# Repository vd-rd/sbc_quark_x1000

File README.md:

## Overview
This module, based on Intel Quark X1020D microprocessor, is intended as a learning exercise in designing an embedded Linux board suitable for IoT applications with a focus on broad connectivity. All the board resources and documentation is open source and can be contributed to.

### Specifications
The board is composed of:
  * Intel Quark X1020 microprocessor
  * 256MB DDR3 RAM
  * NOR flash memory for UEFI and loader
  * MicroSD connector for rootfs and user storage
  * Expansion header with common functions available (USART, SPI, I2C etc.)
  * mPCIexpress header with both full and half size card support.

### Resources
You can find all necesary information to build or evaluate the module here:
   - [View layout and schematic](.) 
   - [View 3D board render](https://a360.co/2vnUFIM)
   - [Fabrication files](https://github.com/vd-rd/sbc_quark_x1000/releases)

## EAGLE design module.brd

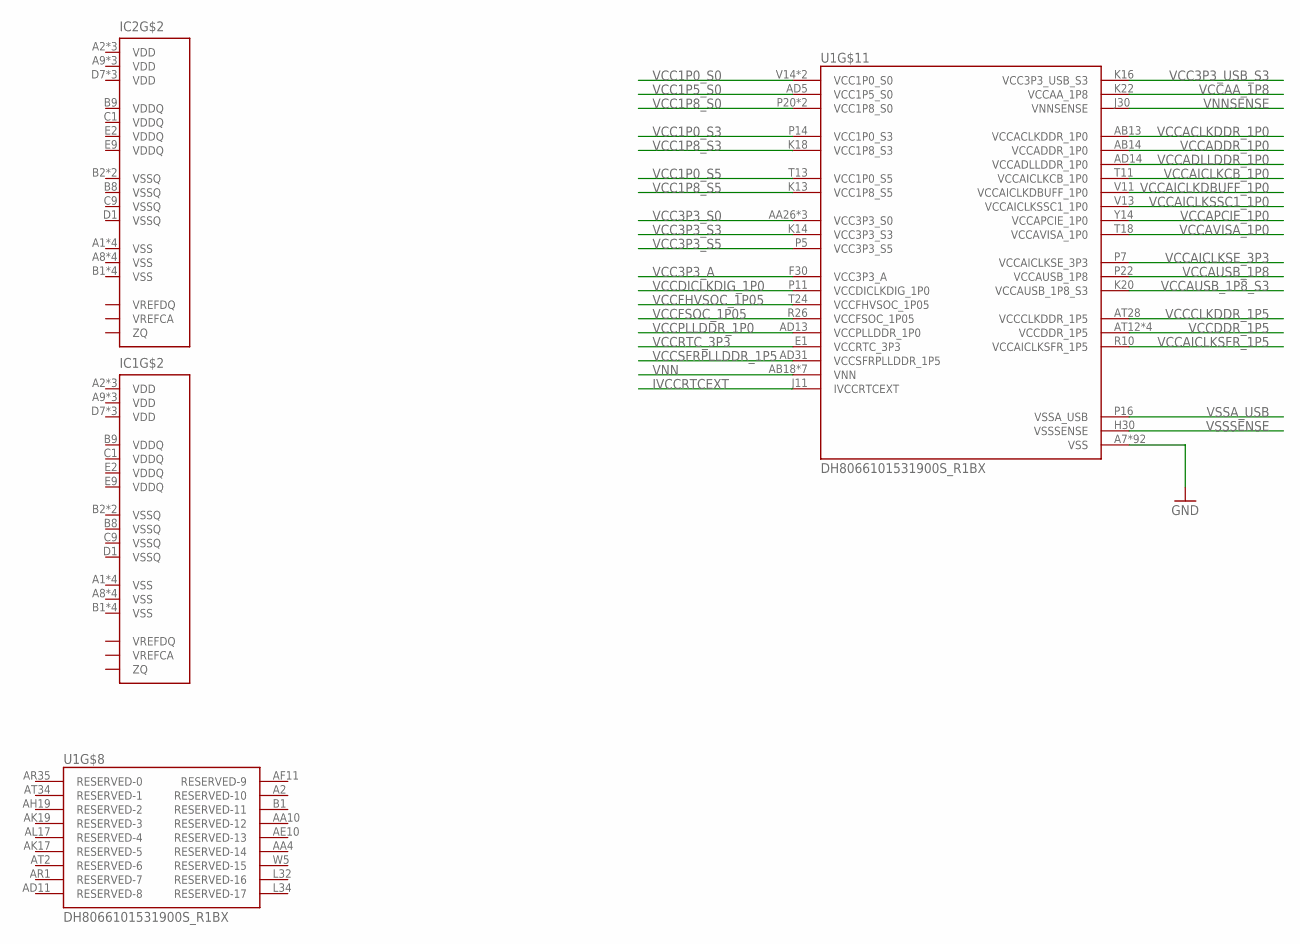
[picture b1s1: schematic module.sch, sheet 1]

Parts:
IC1, IC2: IS43TR82560DL; FBGA78
U1: DH8066101531900S_R1BX; INTEL_DH8066101531900S_R1BX

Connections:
GND: U1.A7 (VSS), U1.A10 (VSS), U1.A12 (VSS), U1.A14 (VSS), U1.A16 (VSS), U1.A18 (VSS), U1.A23 (VSS), U1.A28 (VSS), U1.A31 (VSS), U1.A32 (VSS), U1.A34 (VSS), U1.AB3 (VSS), U1.AB11 (VSS), U1.AB16 (VSS), U1.AB35 (VSS), U1.AC2 (VSS), U1.AC9 (VSS), U1.AC29 (VSS), U1.AC30 (VSS), U1.AD6 (VSS), U1.AD8 (VSS), U1.AD16 (VSS), U1.AD18 (VSS), U1.AD20 (VSS), U1.AD35 (VSS), U1.AE26 (VSS), U1.AF13 (VSS), U1.AF20 (VSS), U1.AF22 (VSS), U1.AF24 (VSS), U1.AG1 (VSS), U1.AG3 (VSS), U1.AH11 (VSS), U1.AH17 (VSS), U1.AJ35 (VSS), U1.AK15 (VSS), U1.AK29 (VSS), U1.AL6 (VSS), U1.AL23 (VSS), U1.AM1 (VSS), U1.AM4 (VSS), U1.AM7 (VSS), U1.AM32 (VSS), U1.AN9 (VSS), U1.AN13 (VSS), U1.AN27 (VSS), U1.AP2 (VSS), U1.AP18 (VSS), U1.AP23 (VSS), U1.AP33 (VSS), U1.AT7 (VSS), U1.B29 (VSS), U1.B31 (VSS), U1.B33 (VSS), U1.B35 (VSS), U1.C1 (VSS), U1.C35 (VSS), U1.D5 (VSS), U1.D29 (VSS), U1.D31 (VSS), U1.D33 (VSS), U1.E32 (VSS), U1.E35 (VSS), U1.F6 (VSS), U1.F32 (VSS), U1.G1 (VSS), U1.G12 (VSS), U1.H17 (VSS), U1.J25 (VSS), U1.K35 (VSS), U1.M1 (VSS), U1.M5 (VSS), U1.M11 (VSS), U1.M13 (VSS), U1.M16 (VSS), U1.M22 (VSS), U1.M28 (VSS), U1.P9 (VSS), U1.P13 (VSS), U1.P27 (VSS), U1.T16 (VSS), U1.T22 (VSS), U1.U1 (VSS), U1.U35 (VSS), U1.V9 (VSS), U1.V22 (VSS), U1.V27 (VSS), U1.W1 (VSS), U1.W27 (VSS), U1.Y11 (VSS), U1.Y13 (VSS), U1.Y22 (VSS); also elsewhere on the board
IVCCRTCEXT: U1.J11 (IVCCRTCEXT)
VCC1P0_S0: U1.V14 (VCC1P0_S0), U1.V16 (VCC1P0_S0)
VCC1P0_S3: U1.P14 (VCC1P0_S3)
VCC1P0_S5: U1.T13 (VCC1P0_S5)
VCC1P5_S0: U1.AD5 (VCC1P5_S0)
VCC1P8_S0: U1.P20 (VCC1P8_S0), U1.T20 (VCC1P8_S0)
VCC1P8_S3: U1.K18 (VCC1P8_S3)
VCC1P8_S5: U1.K13 (VCC1P8_S5)
VCC3P3_A: U1.F30 (VCC3P3_A)
VCC3P3_S0: U1.AA26 (VCC3P3_S0), U1.AB24 (VCC3P3_S0), U1.AD24 (VCC3P3_S0)
VCC3P3_S3: U1.K14 (VCC3P3_S3)
VCC3P3_S5: U1.P5 (VCC3P3_S5)
VCC3P3_USB_S3: U1.K16 (VCC3P3_USB_S3)
VCCAA_1P8: U1.K22 (VCCAA_1P8)
VCCACLKDDR_1P0: U1.AB13 (VCCACLKDDR_1P0)
VCCADDR_1P0: U1.AB14 (VCCADDR_1P0)
VCCADLLDDR_1P0: U1.AD14 (VCCADLLDDR_1P0)
VCCAICLKCB_1P0: U1.T11 (VCCAICLKCB_1P0)
VCCAICLKDBUFF_1P0: U1.V11 (VCCAICLKDBUFF_1P0)
VCCAICLKSE_3P3: U1.P7 (VCCAICLKSE_3P3)
VCCAICLKSFR_1P5: U1.R10 (VCCAICLKSFR_1P5)
VCCAICLKSSC1_1P0: U1.V13 (VCCAICLKSSC1_1P0)
VCCAPCIE_1P0: U1.Y14 (VCCAPCIE_1P0)
VCCAUSB_1P8: U1.P22 (VCCAUSB_1P8)
VCCAUSB_1P8_S3: U1.K20 (VCCAUSB_1P8_S3)
VCCAVISA_1P0: U1.T18 (VCCAVISA_1P0)
VCCCLKDDR_1P5: U1.AT28 (VCCCLKDDR_1P5)
VCCDDR_1P5: U1.AT12 (VCCDDR_1P5), U1.AT16 (VCCDDR_1P5), U1.AT18 (VCCDDR_1P5), U1.AT23 (VCCDDR_1P5)
VCCDICLKDIG_1P0: U1.P11 (VCCDICLKDIG_1P0)
VCCFHVSOC_1P05: U1.T24 (VCCFHVSOC_1P05)
VCCFSOC_1P05: U1.R26 (VCCFSOC_1P05)
VCCPLLDDR_1P0: U1.AD13 (VCCPLLDDR_1P0)
VCCRTC_3P3: U1.E1 (VCCRTC_3P3)
VCCSFRPLLDDR_1P5: U1.AD31 (VCCSFRPLLDDR_1P5)
VDD: IC1.A2 (VDD), IC1.A9 (VDD), IC1.D7 (VDD), IC1.G2 (VDD), IC1.G8 (VDD), IC1.K1 (VDD), IC1.K9 (VDD), IC1.M1 (VDD), IC1.M9 (VDD), IC2.A2 (VDD), IC2.A9 (VDD), IC2.D7 (VDD), IC2.G2 (VDD), IC2.G8 (VDD), IC2.K1 (VDD), IC2.K9 (VDD), IC2.M1 (VDD), IC2.M9 (VDD)
VDDQ: IC1.B9 (VDDQ), IC1.C1 (VDDQ), IC1.E2 (VDDQ), IC1.E9 (VDDQ), IC2.B9 (VDDQ), IC2.C1 (VDDQ), IC2.E2 (VDDQ), IC2.E9 (VDDQ)
VNN: U1.AB18 (VNN), U1.AB20 (VNN), U1.V18 (VNN), U1.V20 (VNN), U1.Y16 (VNN), U1.Y18 (VNN), U1.Y20 (VNN)
VNNSENSE: U1.J30 (VNNSENSE)
VSS: IC1.A1 (VSS), IC1.A8 (VSS), IC1.B1 (VSS), IC1.D8 (VSS), IC1.F2 (VSS), IC1.F8 (VSS), IC1.J1 (VSS), IC1.J9 (VSS), IC1.L1 (VSS), IC1.L9 (VSS), IC1.N1 (VSS), IC1.N9 (VSS), IC2.A1 (VSS), IC2.A8 (VSS), IC2.B1 (VSS), IC2.D8 (VSS), IC2.F2 (VSS), IC2.F8 (VSS), IC2.J1 (VSS), IC2.J9 (VSS), IC2.L1 (VSS), IC2.L9 (VSS), IC2.N1 (VSS), IC2.N9 (VSS)
VSSA_USB: U1.P16 (VSSA_USB)
VSSQ: IC1.B2 (VSSQ), IC1.B8 (VSSQ), IC1.C9 (VSSQ), IC1.D1 (VSSQ), IC1.D9 (VSSQ), IC2.B2 (VSSQ), IC2.B8 (VSSQ), IC2.C9 (VSSQ), IC2.D1 (VSSQ), IC2.D9 (VSSQ)
VSSSENSE: U1.H30 (VSSSENSE)

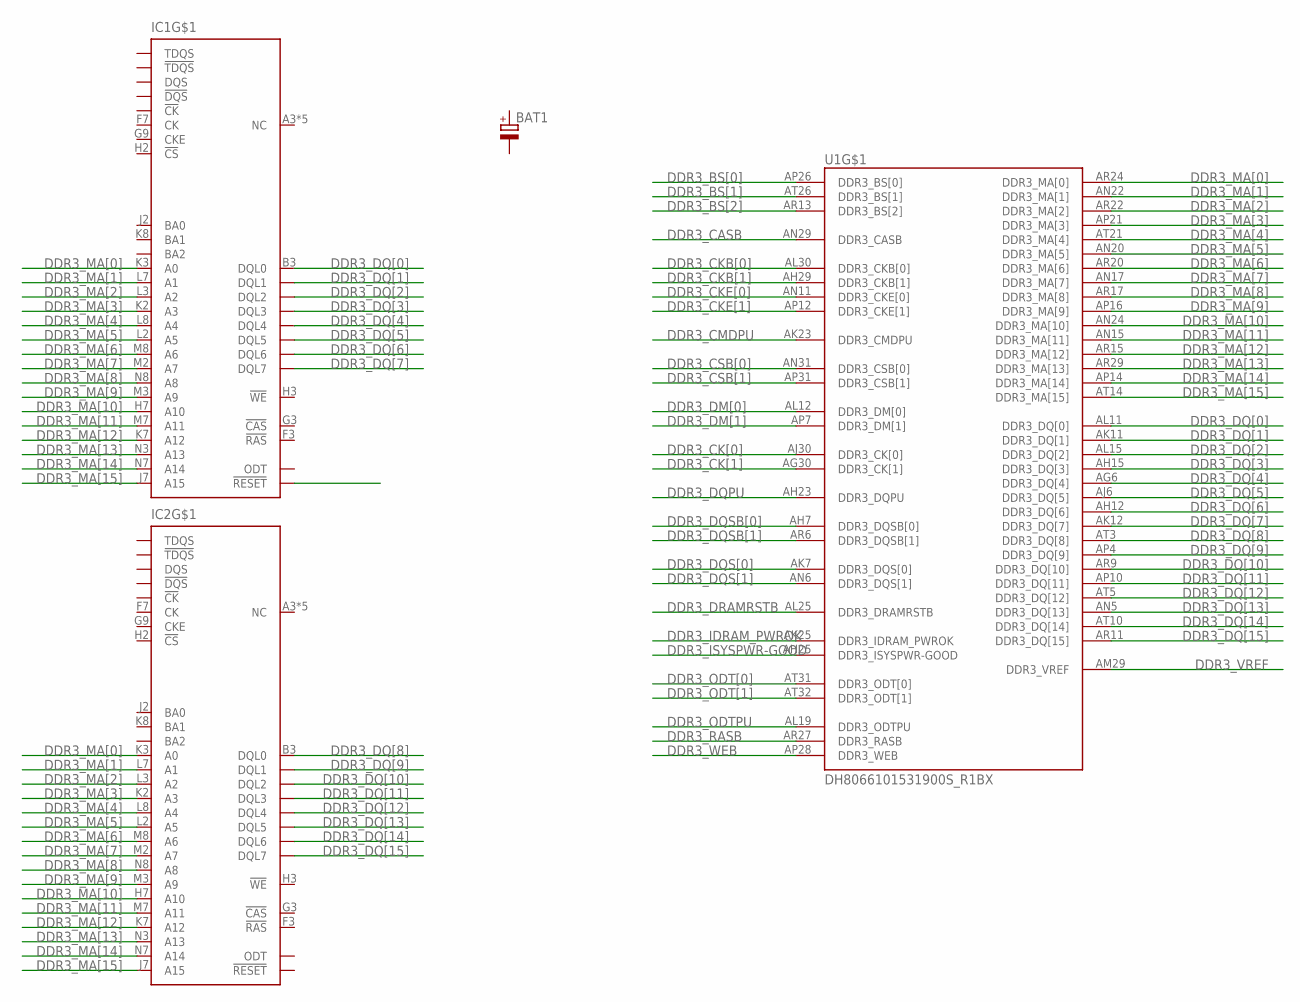
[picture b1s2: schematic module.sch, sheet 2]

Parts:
BAT1: DCK-3R3E224U-E; 621
IC1, IC2: IS43TR82560DL; FBGA78
U1: DH8066101531900S_R1BX; INTEL_DH8066101531900S_R1BX

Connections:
DDR3_BS[0]: U1.AP26 (DDR3_BS[0])
DDR3_BS[1]: U1.AT26 (DDR3_BS[1])
DDR3_BS[2]: U1.AR13 (DDR3_BS[2])
DDR3_CASB: U1.AN29 (DDR3_CASB)
DDR3_CKB[0]: U1.AL30 (DDR3_CKB[0])
DDR3_CKB[1]: U1.AH29 (DDR3_CKB[1])
DDR3_CKE[0]: U1.AN11 (DDR3_CKE[0])
DDR3_CKE[1]: U1.AP12 (DDR3_CKE[1])
DDR3_CK[0]: U1.AJ30 (DDR3_CK[0])
DDR3_CK[1]: U1.AG30 (DDR3_CK[1])
DDR3_CMDPU: U1.AK23 (DDR3_CMDPU)
DDR3_CSB[0]: U1.AN31 (DDR3_CSB[0])
DDR3_CSB[1]: U1.AP31 (DDR3_CSB[1])
DDR3_DM[0]: U1.AL12 (DDR3_DM[0])
DDR3_DM[1]: U1.AP7 (DDR3_DM[1])
DDR3_DQPU: U1.AH23 (DDR3_DQPU)
DDR3_DQSB[0]: U1.AH7 (DDR3_DQSB[0])
DDR3_DQSB[1]: U1.AR6 (DDR3_DQSB[1])
DDR3_DQS[0]: U1.AK7 (DDR3_DQS[0])
DDR3_DQS[1]: U1.AN6 (DDR3_DQS[1])
DDR3_DQ[0]: IC1.B3 (DQL0), U1.AL11 (DDR3_DQ[0])
DDR3_DQ[1]: IC1.C7 (DQL1), U1.AK11 (DDR3_DQ[1])
DDR3_DQ[2]: IC1.C2 (DQL2), U1.AL15 (DDR3_DQ[2])
DDR3_DQ[3]: IC1.C8 (DQL3), U1.AH15 (DDR3_DQ[3])
DDR3_DQ[4]: IC1.E3 (DQL4), U1.AG6 (DDR3_DQ[4])
DDR3_DQ[5]: IC1.E8 (DQL5), U1.AJ6 (DDR3_DQ[5])
DDR3_DQ[6]: IC1.D2 (DQL6), U1.AH12 (DDR3_DQ[6])
DDR3_DQ[7]: IC1.E7 (DQL7), U1.AK12 (DDR3_DQ[7])
DDR3_DQ[8]: IC2.B3 (DQL0), U1.AT3 (DDR3_DQ[8])
DDR3_DQ[9]: IC2.C7 (DQL1), U1.AP4 (DDR3_DQ[9])
DDR3_DQ[10]: IC2.C2 (DQL2), U1.AR9 (DDR3_DQ[10])
DDR3_DQ[11]: IC2.C8 (DQL3), U1.AP10 (DDR3_DQ[11])
DDR3_DQ[12]: IC2.E3 (DQL4), U1.AT5 (DDR3_DQ[12])
DDR3_DQ[13]: IC2.E8 (DQL5), U1.AN5 (DDR3_DQ[13])
DDR3_DQ[14]: IC2.D2 (DQL6), U1.AT10 (DDR3_DQ[14])
DDR3_DQ[15]: IC2.E7 (DQL7), U1.AR11 (DDR3_DQ[15])
DDR3_DRAMRSTB: U1.AL25 (DDR3_DRAMRSTB)
DDR3_IDRAM_PWROK: U1.AK25 (DDR3_IDRAM_PWROK)
DDR3_ISYSPWR-GOOD: U1.AH25 (DDR3_ISYSPWR-GOOD)
DDR3_MA[0]: IC1.K3 (A0), IC2.K3 (A0), U1.AR24 (DDR3_MA[0])
DDR3_MA[1]: IC1.L7 (A1), IC2.L7 (A1), U1.AN22 (DDR3_MA[1])
DDR3_MA[2]: IC1.L3 (A2), IC2.L3 (A2), U1.AR22 (DDR3_MA[2])
DDR3_MA[3]: IC1.K2 (A3), IC2.K2 (A3), U1.AP21 (DDR3_MA[3])
DDR3_MA[4]: IC1.L8 (A4), IC2.L8 (A4), U1.AT21 (DDR3_MA[4])
DDR3_MA[5]: IC1.L2 (A5), IC2.L2 (A5), U1.AN20 (DDR3_MA[5])
DDR3_MA[6]: IC1.M8 (A6), IC2.M8 (A6), U1.AR20 (DDR3_MA[6])
DDR3_MA[7]: IC1.M2 (A7), IC2.M2 (A7), U1.AN17 (DDR3_MA[7])
DDR3_MA[8]: IC1.N8 (A8), IC2.N8 (A8), U1.AR17 (DDR3_MA[8])
DDR3_MA[9]: IC1.M3 (A9), IC2.M3 (A9), U1.AP16 (DDR3_MA[9])
DDR3_MA[10]: IC1.H7 (A10), IC2.H7 (A10), U1.AN24 (DDR3_MA[10])
DDR3_MA[11]: IC1.M7 (A11), IC2.M7 (A11), U1.AN15 (DDR3_MA[11])
DDR3_MA[12]: IC1.K7 (A12), IC2.K7 (A12), U1.AR15 (DDR3_MA[12])
DDR3_MA[13]: IC1.N3 (A13), IC2.N3 (A13), U1.AR29 (DDR3_MA[13])
DDR3_MA[14]: IC1.N7 (A14), IC2.N7 (A14), U1.AP14 (DDR3_MA[14])
DDR3_MA[15]: IC1.J7 (A15), IC2.J7 (A15), U1.AT14 (DDR3_MA[15])
DDR3_ODTPU: U1.AL19 (DDR3_ODTPU)
DDR3_ODT[0]: U1.AT31 (DDR3_ODT[0])
DDR3_ODT[1]: U1.AT32 (DDR3_ODT[1])
DDR3_RASB: U1.AR27 (DDR3_RASB)
DDR3_VREF: U1.AM29 (DDR3_VREF)
DDR3_WEB: U1.AP28 (DDR3_WEB)
VDD: IC1.A2 (VDD), IC1.A9 (VDD), IC1.D7 (VDD), IC1.G2 (VDD), IC1.G8 (VDD), IC1.K1 (VDD), IC1.K9 (VDD), IC1.M1 (VDD), IC1.M9 (VDD), IC2.A2 (VDD), IC2.A9 (VDD), IC2.D7 (VDD), IC2.G2 (VDD), IC2.G8 (VDD), IC2.K1 (VDD), IC2.K9 (VDD), IC2.M1 (VDD), IC2.M9 (VDD)
VDDQ: IC1.B9 (VDDQ), IC1.C1 (VDDQ), IC1.E2 (VDDQ), IC1.E9 (VDDQ), IC2.B9 (VDDQ), IC2.C1 (VDDQ), IC2.E2 (VDDQ), IC2.E9 (VDDQ)
VSS: IC1.A1 (VSS), IC1.A8 (VSS), IC1.B1 (VSS), IC1.D8 (VSS), IC1.F2 (VSS), IC1.F8 (VSS), IC1.J1 (VSS), IC1.J9 (VSS), IC1.L1 (VSS), IC1.L9 (VSS), IC1.N1 (VSS), IC1.N9 (VSS), IC2.A1 (VSS), IC2.A8 (VSS), IC2.B1 (VSS), IC2.D8 (VSS), IC2.F2 (VSS), IC2.F8 (VSS), IC2.J1 (VSS), IC2.J9 (VSS), IC2.L1 (VSS), IC2.L9 (VSS), IC2.N1 (VSS), IC2.N9 (VSS)
VSSQ: IC1.B2 (VSSQ), IC1.B8 (VSSQ), IC1.C9 (VSSQ), IC1.D1 (VSSQ), IC1.D9 (VSSQ), IC2.B2 (VSSQ), IC2.B8 (VSSQ), IC2.C9 (VSSQ), IC2.D1 (VSSQ), IC2.D9 (VSSQ)

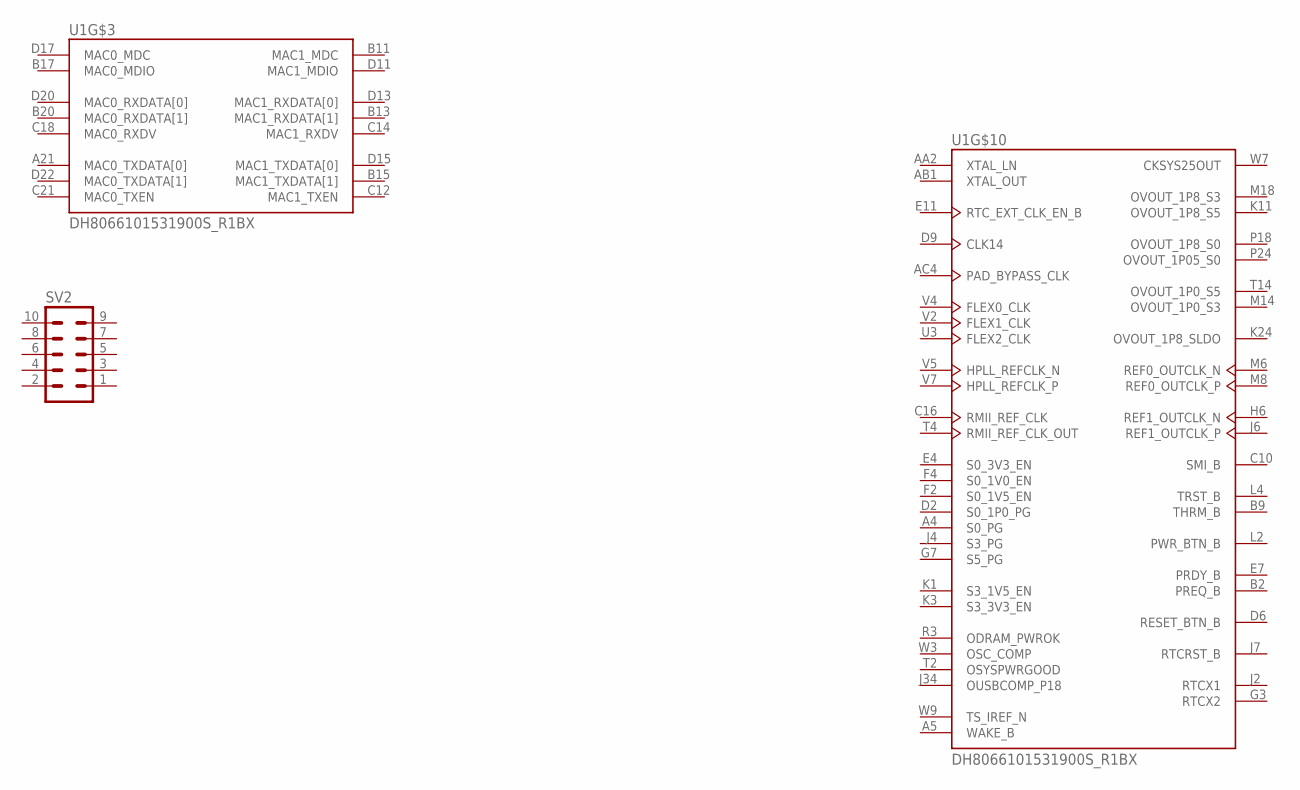
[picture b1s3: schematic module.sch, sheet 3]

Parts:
SV2: MA05-2
U1: DH8066101531900S_R1BX; INTEL_DH8066101531900S_R1BX

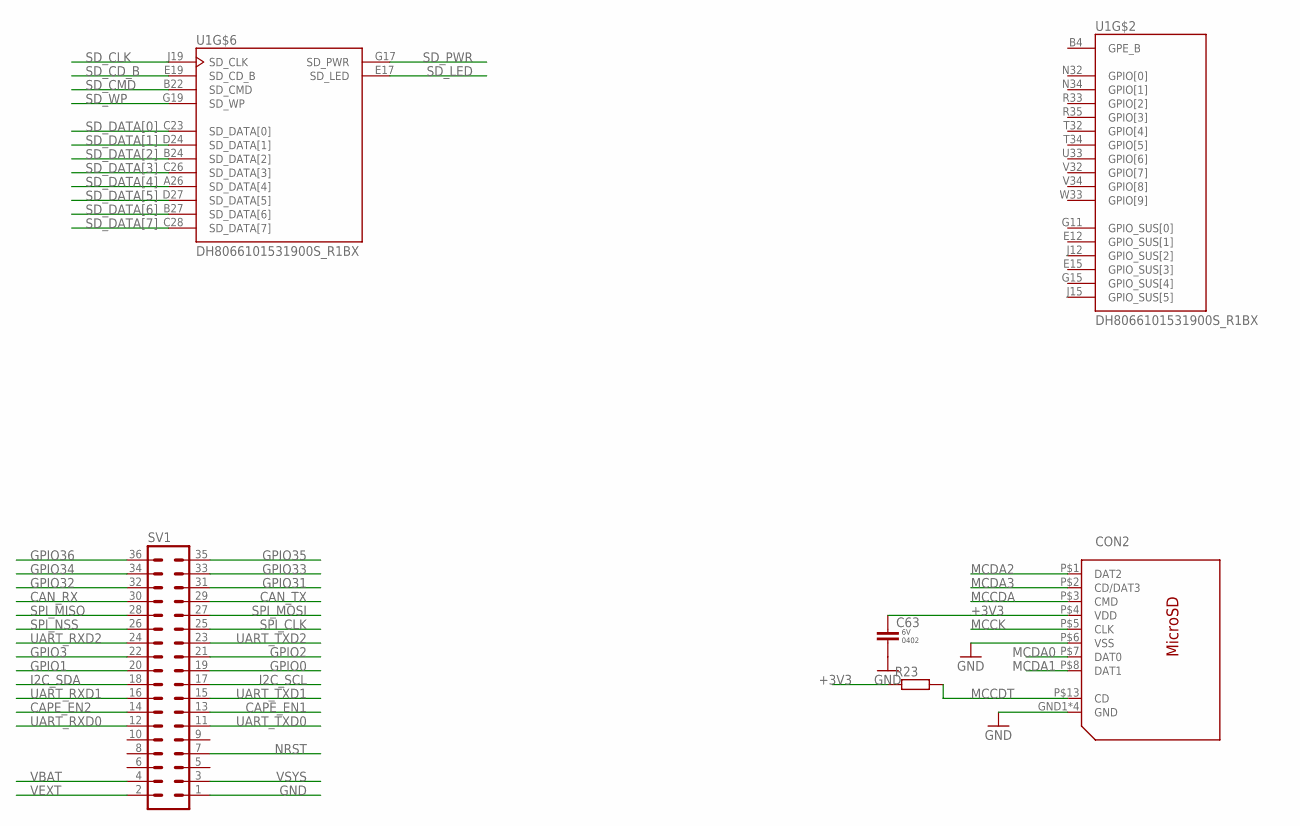
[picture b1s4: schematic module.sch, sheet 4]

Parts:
C63: CAP-0402; C0402K
CON2: 112J-TXAR; 112J
R23: R-EU_R0402; R0402
SV1: MA18-2
U1: DH8066101531900S_R1BX; INTEL_DH8066101531900S_R1BX

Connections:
+3V3: C63.1, CON2.P$4 (VDD), R23.1
CAN_RX: SV1.30
CAN_TX: SV1.29
CAPE_EN1: SV1.13
CAPE_EN2: SV1.14
GND: C63.2, CON2.GND1 (GND), CON2.GND2 (GND), CON2.GND3 (GND), CON2.GND4 (GND), CON2.P$6 (VSS), SV1.1; also elsewhere on the board
GPIO0: SV1.19
GPIO1: SV1.20
GPIO2: SV1.21
GPIO3: SV1.22
GPIO31: SV1.31
GPIO32: SV1.32
GPIO33: SV1.33
GPIO34: SV1.34
GPIO35: SV1.35
GPIO36: SV1.36
I2C_SCL: SV1.17
I2C_SDA: SV1.18
MCCDA: CON2.P$3 (CMD)
MCCDT: CON2.P$13 (CD), R23.2
MCCK: CON2.P$5 (CLK)
MCDA0: CON2.P$7 (DAT0)
MCDA1: CON2.P$8 (DAT1)
MCDA2: CON2.P$1 (DAT2)
MCDA3: CON2.P$2 (CD/DAT3)
NRST: SV1.7
SD_CD_B: U1.E19 (SD_CD_B)
SD_CLK: U1.J19 (SD_CLK)
SD_CMD: U1.B22 (SD_CMD)
SD_DATA[0]: U1.C23 (SD_DATA[0])
SD_DATA[1]: U1.D24 (SD_DATA[1])
SD_DATA[2]: U1.B24 (SD_DATA[2])
SD_DATA[3]: U1.C26 (SD_DATA[3])
SD_DATA[4]: U1.A26 (SD_DATA[4])
SD_DATA[5]: U1.D27 (SD_DATA[5])
SD_DATA[6]: U1.B27 (SD_DATA[6])
SD_DATA[7]: U1.C28 (SD_DATA[7])
SD_LED: U1.E17 (SD_LED)
SD_PWR: U1.G17 (SD_PWR)
SD_WP: U1.G19 (SD_WP)
SPI_CLK: SV1.25
SPI_MISO: SV1.28
SPI_MOSI: SV1.27
SPI_NSS: SV1.26
UART_RXD0: SV1.12
UART_RXD1: SV1.16
UART_RXD2: SV1.24
UART_TXD0: SV1.11
UART_TXD1: SV1.15
UART_TXD2: SV1.23
VBAT: SV1.4
VEXT: SV1.2
VSYS: SV1.3

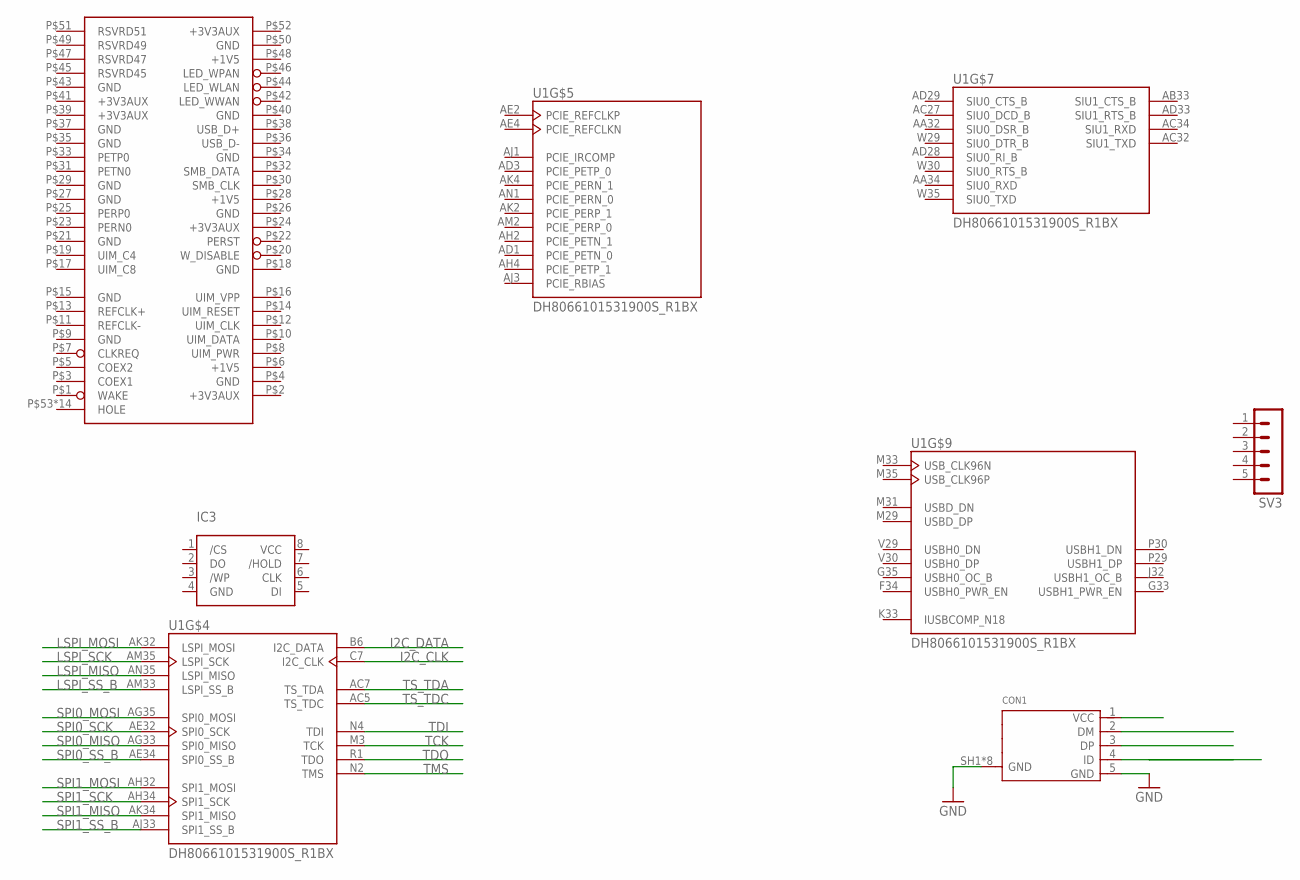
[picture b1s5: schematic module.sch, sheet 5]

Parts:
CON1: 10118194-0001LF; 10118194
IC3: W25Q128JV; SO08-208
PCI1: 119A-XXA00; 119A
SV3: MA05-1
U1: DH8066101531900S_R1BX; INTEL_DH8066101531900S_R1BX

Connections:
+1V5: PCI1.P$6 (+1V5), PCI1.P$28 (+1V5)
+3V3AUX: PCI1.P$2 (+3V3AUX), PCI1.P$24 (+3V3AUX), PCI1.P$52 (+3V3AUX)
GND: CON1.5 (GND), CON1.SH1 (GND), CON1.SH2 (GND), CON1.SH3 (GND), CON1.SH4 (GND), CON1.SH5 (GND), CON1.SH6 (GND), CON1.SH7 (GND), CON1.SH8 (GND), PCI1.P$4 (GND), PCI1.P$9 (GND), PCI1.P$15 (GND), PCI1.P$18 (GND), PCI1.P$21 (GND), PCI1.P$26 (GND), PCI1.P$27 (GND), PCI1.P$29 (GND), PCI1.P$35 (GND); also elsewhere on the board
I2C_CLK: U1.C7 (I2C_CLK)
I2C_DATA: U1.B6 (I2C_DATA)
LSPI_MISO: U1.AN35 (LSPI_MISO)
LSPI_MOSI: U1.AK32 (LSPI_MOSI)
LSPI_SCK: U1.AM35 (LSPI_SCK)
LSPI_SS_B: U1.AM33 (LSPI_SS_B)
SMB_DATA: PCI1.P$32 (SMB_DATA)
SPI0_MISO: U1.AG33 (SPI0_MISO)
SPI0_MOSI: U1.AG35 (SPI0_MOSI)
SPI0_SCK: U1.AE32 (SPI0_SCK)
SPI0_SS_B: U1.AE34 (SPI0_SS_B)
SPI1_MISO: U1.AK34 (SPI1_MISO)
SPI1_MOSI: U1.AH32 (SPI1_MOSI)
SPI1_SCK: U1.AH34 (SPI1_SCK)
SPI1_SS_B: U1.AJ33 (SPI1_SS_B)
TCK: U1.M3 (TCK)
TDI: U1.N4 (TDI)
TDO: U1.R1 (TDO)
TMS: U1.N2 (TMS)
TS_TDA: U1.AC7 (TS_TDA)
TS_TDC: U1.AC5 (TS_TDC)
USBC_DM: CON1.2 (DM)
USBC_DP: CON1.3 (DP)
USBC_ID: CON1.4 (ID)
USB_D+: PCI1.P$38 (USB_D+)

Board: 4 copper layers, 13 parts (1 on the bottom side), 46 nets, no tracks yet.

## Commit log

2019-04-24 board: initial upload
2019-04-24 board: defined mechanical form
2019-04-24 board: added mpci port
2019-04-24 schematic: symbol pin breakout
2019-04-24 board: added ddr3 ram
2019-04-24 board: add uefi flash
2019-04-24 schematic: ddr signal connections
2019-04-25 schematic: rearranged symbols
